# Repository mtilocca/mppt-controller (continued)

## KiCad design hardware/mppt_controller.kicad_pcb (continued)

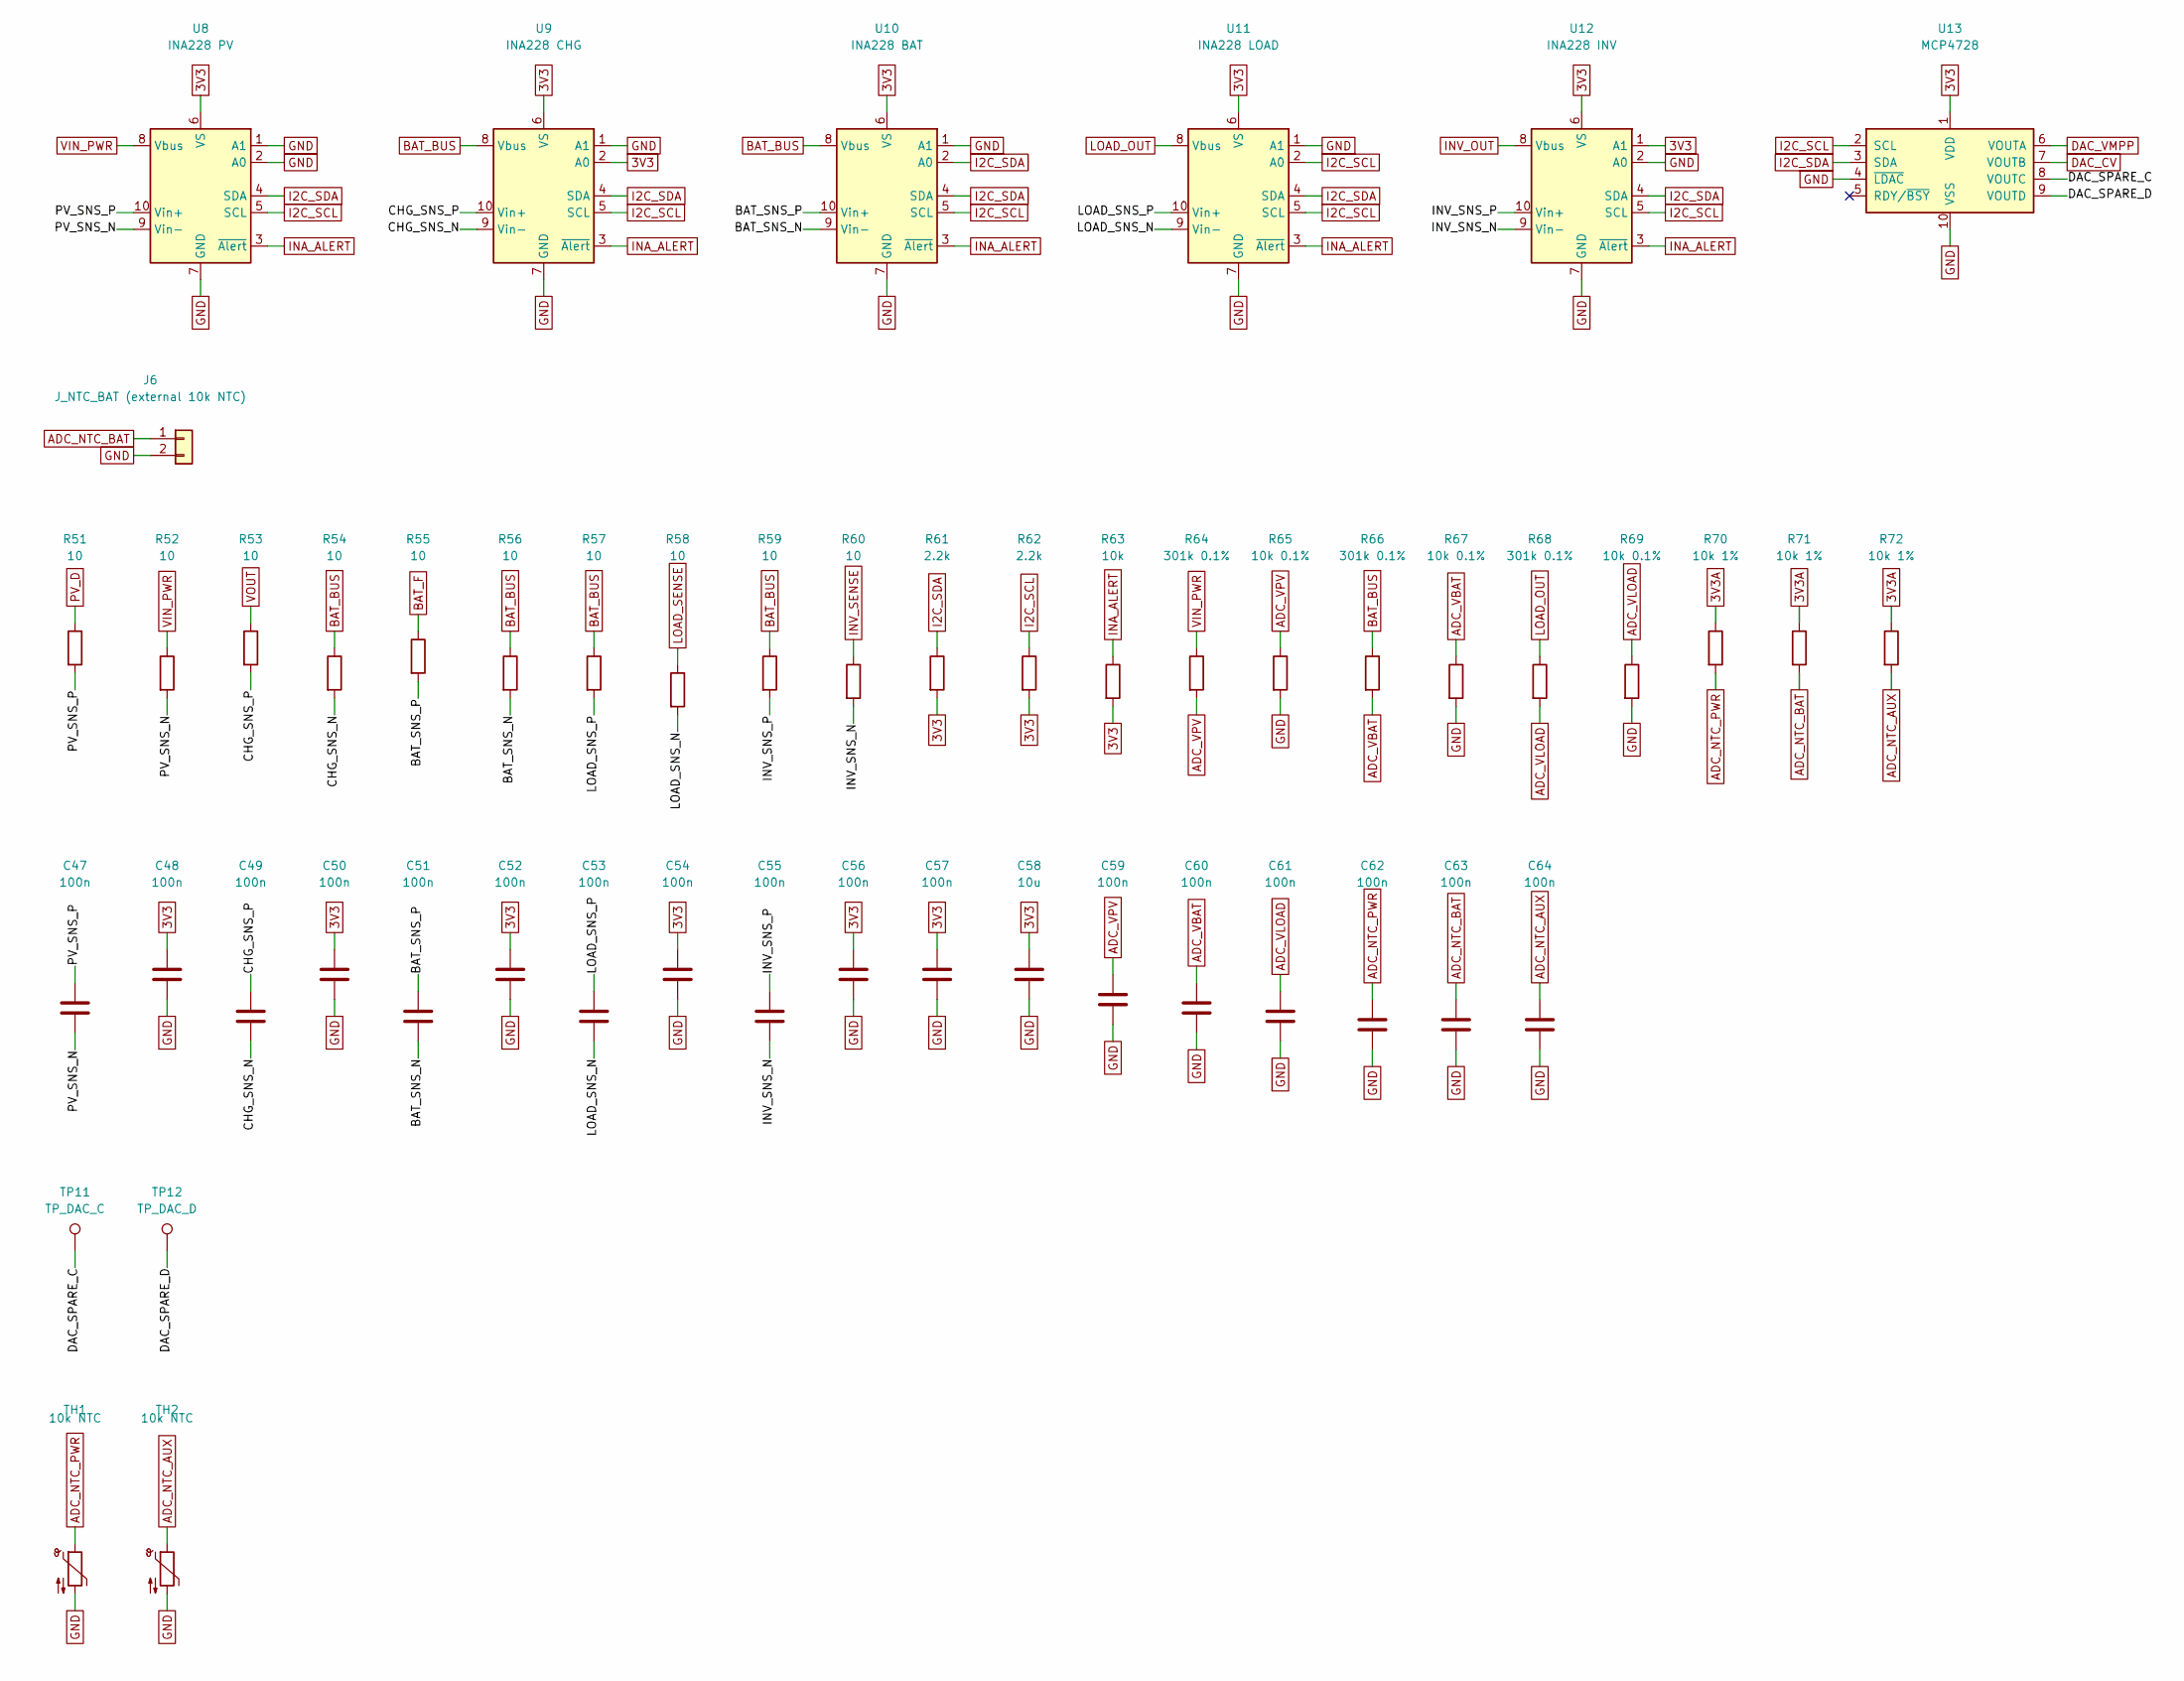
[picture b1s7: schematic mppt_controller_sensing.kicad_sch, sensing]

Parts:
C47, C48, C49, C50, C51, C52, C53, C54, C55, C56, C57, C59, C60, C61, C62, C63, C64: 100n; C_0603_1608Metric
C58: 10u; C_0805_2012Metric
J6: J_NTC_BAT (external 10k NTC); PinHeader_1x02_P2.54mm_Vertical
R51, R52, R53, R54, R55, R56, R57, R58, R59, R60: 10; R_0603_1608Metric
R61, R62: 2.2k; R_0603_1608Metric
R63: 10k; R_0603_1608Metric
R64, R66, R68: 301k 0.1%; R_0603_1608Metric
R65, R67, R69: 10k 0.1%; R_0603_1608Metric
R70, R71, R72: 10k 1%; R_0603_1608Metric
TH1, TH2: 10k NTC; R_0603_1608Metric
TP11: TP_DAC_C; TestPoint_Pad_D1.5mm
TP12: TP_DAC_D; TestPoint_Pad_D1.5mm
U8: INA228 PV; MSOP-10_3x3mm_P0.5mm
U9: INA228 CHG; MSOP-10_3x3mm_P0.5mm
U10: INA228 BAT; MSOP-10_3x3mm_P0.5mm
U11: INA228 LOAD; MSOP-10_3x3mm_P0.5mm
U12: INA228 INV; MSOP-10_3x3mm_P0.5mm
U13: MCP4728; MSOP-10_3x3mm_P0.5mm

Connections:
3V3: C48.1, C50.1, C52.1, C54.1, C56.1, C57.1, C58.1, R61.2, R62.2, R63.2, U8.6 (VS), U9.2 (A0), U9.6 (VS), U10.6 (VS), U11.6 (VS), U12.1 (A1), U12.6 (VS), U13.1 (VDD); also elsewhere on the board
3V3A: R70.1, R71.1, R72.1; also elsewhere on the board
/sensing/BAT_SNS_N: C51.2, R56.2, U10.9 (Vin-)
/sensing/BAT_SNS_P: C51.1, R55.2, U10.10 (Vin+)
/sensing/CHG_SNS_N: C49.2, R54.2, U9.9 (Vin-)
/sensing/CHG_SNS_P: C49.1, R53.2, U9.10 (Vin+)
/sensing/DAC_SPARE_C: TP11.1, U13.8 (VOUTC)
/sensing/DAC_SPARE_D: TP12.1, U13.9 (VOUTD)
/sensing/INV_SNS_N: C55.2, R60.2, U12.9 (Vin-)
/sensing/INV_SNS_P: C55.1, R59.2, U12.10 (Vin+)
/sensing/LOAD_SNS_N: C53.2, R58.2, U11.9 (Vin-)
/sensing/LOAD_SNS_P: C53.1, R57.2, U11.10 (Vin+)
/sensing/PV_SNS_N: C47.2, R52.2, U8.9 (Vin-)
/sensing/PV_SNS_P: C47.1, R51.2, U8.10 (Vin+)
ADC_NTC_AUX: C64.1, R72.2, TH2.1; also elsewhere on the board
ADC_NTC_BAT: C63.1, J6.1, R71.2; also elsewhere on the board
ADC_NTC_PWR: C62.1, R70.2, TH1.1; also elsewhere on the board
ADC_VBAT: C60.1, R66.2, R67.1; also elsewhere on the board
ADC_VLOAD: C61.1, R68.2, R69.1; also elsewhere on the board
ADC_VPV: C59.1, R64.2, R65.1; also elsewhere on the board
BAT_BUS: R54.1, R56.1, R57.1, R59.1, R66.1, U9.8 (Vbus), U10.8 (Vbus); also elsewhere on the board
BAT_F: R55.1; also elsewhere on the board
DAC_CV: U13.7 (VOUTB); also elsewhere on the board
DAC_VMPP: U13.6 (VOUTA); also elsewhere on the board
GND: C48.2, C50.2, C52.2, C54.2, C56.2, C57.2, C58.2, C59.2, C60.2, C61.2, C62.2, C63.2, C64.2, J6.2, R65.2, R67.2, R69.2, TH1.2, TH2.2, U8.1 (A1), U8.2 (A0), U8.7 (GND), U9.1 (A1), U9.7 (GND), U10.1 (A1), U10.7 (GND), U11.1 (A1), U11.7 (GND), U12.2 (A0), U12.7 (GND), U13.4 (~LDAC), U13.10 (VSS); also elsewhere on the board
I2C_SCL: R62.1, U8.5 (SCL), U9.5 (SCL), U10.5 (SCL), U11.2 (A0), U11.5 (SCL), U12.5 (SCL), U13.2 (SCL); also elsewhere on the board
I2C_SDA: R61.1, U8.4 (SDA), U9.4 (SDA), U10.2 (A0), U10.4 (SDA), U11.4 (SDA), U12.4 (SDA), U13.3 (SDA); also elsewhere on the board
INA_ALERT: R63.1, U8.3 (~Alert), U9.3 (~Alert), U10.3 (~Alert), U11.3 (~Alert), U12.3 (~Alert); also elsewhere on the board
INV_OUT: U12.8 (Vbus); also elsewhere on the board
INV_SENSE: R60.1; also elsewhere on the board
LOAD_OUT: R68.1, U11.8 (Vbus); also elsewhere on the board
LOAD_SENSE: R58.1; also elsewhere on the board
PV_D: R51.1; also elsewhere on the board
VIN_PWR: R52.1, R64.1, U8.8 (Vbus); also elsewhere on the board
VOUT: R53.1; also elsewhere on the board

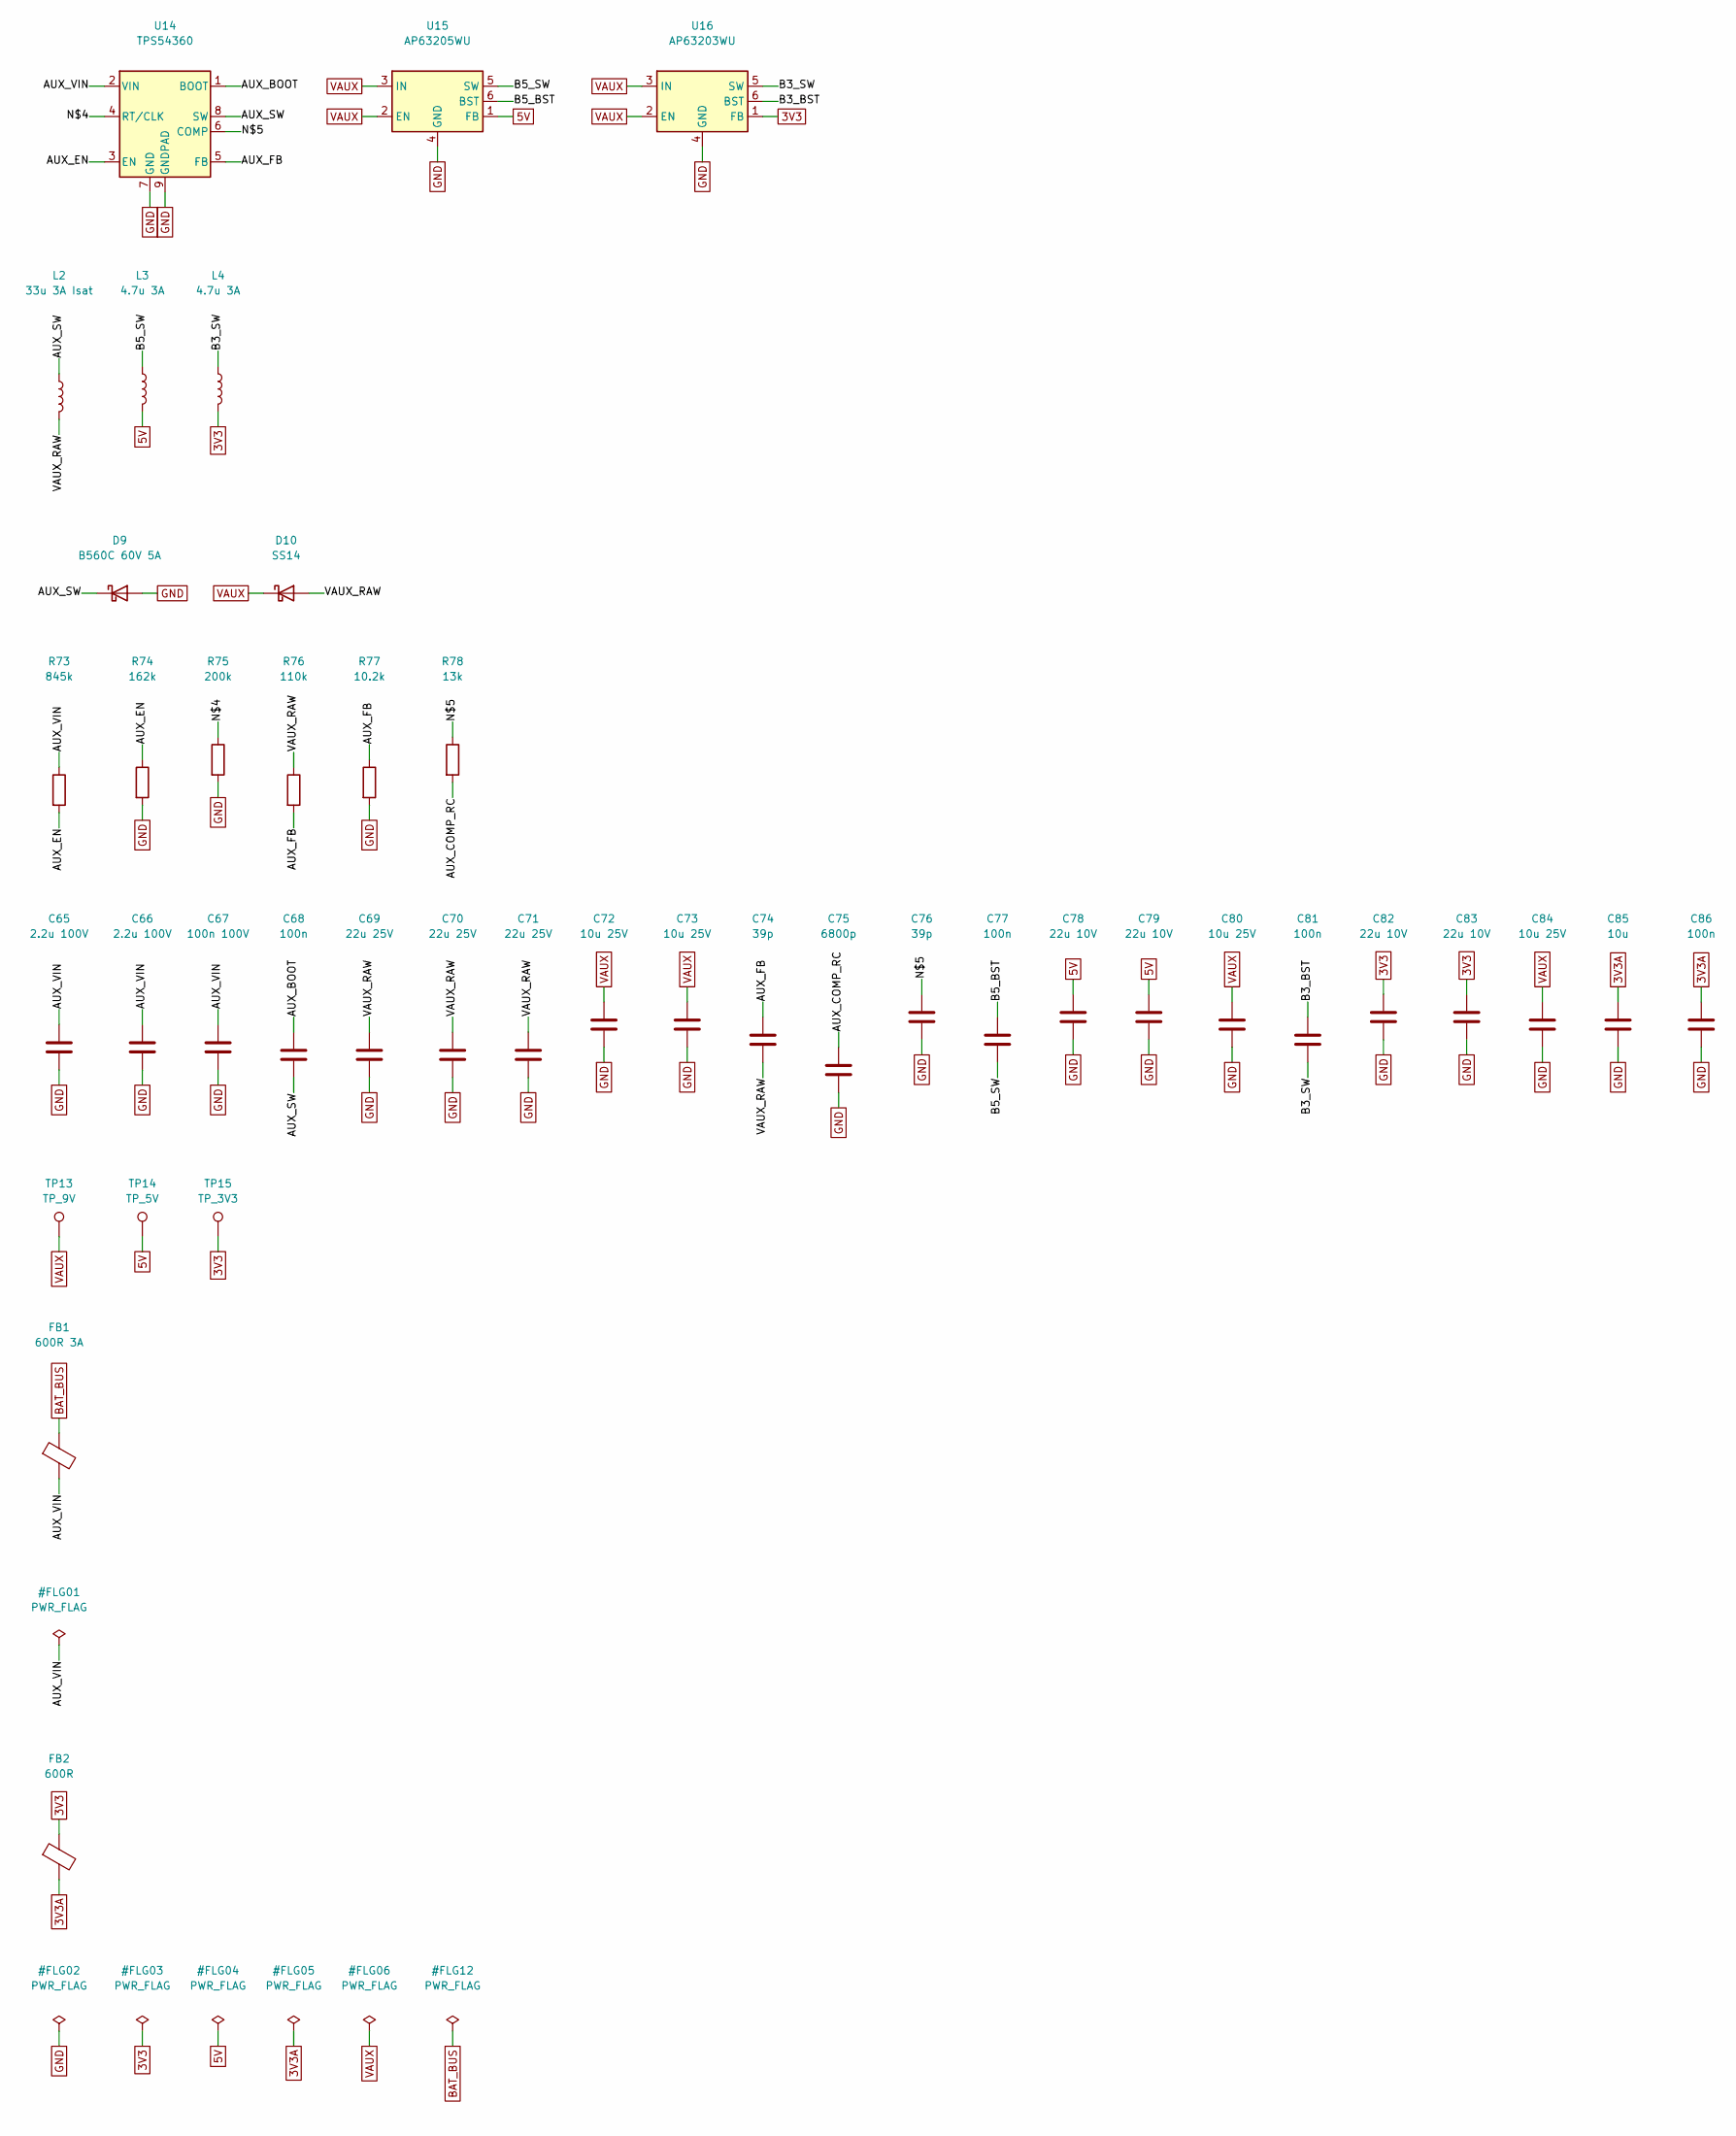
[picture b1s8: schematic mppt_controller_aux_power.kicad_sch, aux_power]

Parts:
C65, C66: 2.2u 100V; C_1210_3225Metric
C67: 100n 100V; C_0805_2012Metric
C68, C77, C81, C86: 100n; C_0603_1608Metric
C69, C70, C71: 22u 25V; C_1210_3225Metric
C72, C73, C80, C84: 10u 25V; C_1206_3216Metric
C74, C76: 39p; C_0603_1608Metric
C75: 6800p; C_0603_1608Metric
C78, C79, C82, C83: 22u 10V; C_1206_3216Metric
C85: 10u; C_0805_2012Metric
D9: B560C 60V 5A; D_SMC
D10: SS14; D_SMA
FB1: 600R 3A; L_1206_3216Metric
FB2: 600R; L_0603_1608Metric
L2: 33u 3A Isat; L_Bourns_SRP1245A
L3, L4: 4.7u 3A; L_Bourns_SRP5030T
R73: 845k; R_0603_1608Metric
R74: 162k; R_0603_1608Metric
R75: 200k; R_0603_1608Metric
R76: 110k; R_0603_1608Metric
R77: 10.2k; R_0603_1608Metric
R78: 13k; R_0603_1608Metric
TP13: TP_9V; TestPoint_Pad_D1.5mm
TP14: TP_5V; TestPoint_Pad_D1.5mm
TP15: TP_3V3; TestPoint_Pad_D1.5mm
U14: TPS54360; HSOP-8-1EP_3.9x4.9mm_P1.27mm_EP2.41x3.1mm
U15: AP63205WU; TSOT-23-6
U16: AP63203WU; TSOT-23-6

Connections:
3V3: C82.1, C83.1, FB2.1, L4.2, TP15.1, U16.1 (FB); also elsewhere on the board
3V3A: C85.1, C86.1, FB2.2; also elsewhere on the board
5V: C78.1, C79.1, L3.2, TP14.1, U15.1 (FB); also elsewhere on the board
/aux_power/AUX_BOOT: C68.1, U14.1 (BOOT)
/aux_power/AUX_COMP_RC: C75.1, R78.2
/aux_power/AUX_EN: R73.2, R74.1, U14.3 (EN)
/aux_power/AUX_FB: C74.1, R76.2, R77.1, U14.5 (FB)
/aux_power/AUX_SW: C68.2, D9.1 (K), L2.1, U14.8 (SW)
/aux_power/AUX_VIN: C65.1, C66.1, C67.1, FB1.2, R73.1, U14.2 (VIN)
/aux_power/B3_BST: C81.1, U16.6 (BST)
/aux_power/B3_SW: C81.2, L4.1, U16.5 (SW)
/aux_power/B5_BST: C77.1, U15.6 (BST)
/aux_power/B5_SW: C77.2, L3.1, U15.5 (SW)
/aux_power/N$4: R75.1, U14.4 (RT/CLK)
/aux_power/N$5: C76.1, R78.1, U14.6 (COMP)
/aux_power/VAUX_RAW: C69.1, C70.1, C71.1, C74.2, D10.2 (A), L2.2, R76.1
BAT_BUS: FB1.1; also elsewhere on the board
GND: C65.2, C66.2, C67.2, C69.2, C70.2, C71.2, C72.2, C73.2, C75.2, C76.2, C78.2, C79.2, C80.2, C82.2, C83.2, C84.2, C85.2, C86.2, D9.2 (A), R74.2, R75.2, R77.2, U14.7 (GND), U14.9 (GNDPAD), U15.4 (GND), U16.4 (GND); also elsewhere on the board
VAUX: C72.1, C73.1, C80.1, C84.1, D10.1 (K), TP13.1, U15.2 (EN), U15.3 (IN), U16.2 (EN), U16.3 (IN); also elsewhere on the board

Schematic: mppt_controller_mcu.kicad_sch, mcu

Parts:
C87, C88: 2.2u; C_0603_1608Metric
C89, C90, C91, C92, C93, C94, C95, C96, C97, C98, C99, C103, C104: 100n; C_0603_1608Metric
C100, C101: 4.7u; C_0805_2012Metric
C102: 1u; C_0603_1608Metric
C105, C106: 12p; C_0603_1608Metric
C107, C108: 8p; C_0603_1608Metric
J7: J_SWD (Cortex 1.27 mm); PinHeader_2x05_P1.27mm_Vertical
R79: 10k; R_0603_1608Metric
R80: 1k; R_0603_1608Metric
SW1: RESET; SW_SPST_PTS645Sx43SMTR92
SW2: BOOT0; SW_SPST_PTS645Sx43SMTR92
U17: STM32H743ZIT6; LQFP-144_20x20mm_P0.5mm
Y1: 25MHz 8pF; Crystal_SMD_3225-4Pin_3.2x2.5mm
Y2: 32.768kHz 6pF; Crystal_SMD_3215-2Pin_3.2x1.5mm

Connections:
3V3: C89.1, C90.1, C91.1, C92.1, C93.1, C94.1, C95.1, C96.1, C97.1, C98.1, C99.1, C100.1, C101.1, J7.1, R80.2, U17.6 (VBAT), U17.17 (VDD), U17.30 (VDD), U17.39 (VDD), U17.52 (VDD), U17.62 (VDD), U17.72 (VDD), U17.84 (VDD), U17.95 (VDD33_USB), U17.108 (VDD), U17.121 (VDD), U17.131 (VDD), U17.143 (PDR_ON), U17.144 (VDD); also elsewhere on the board
3V3A: C102.1, C103.1, U17.32 (VREF+), U17.33 (VDDA); also elsewhere on the board
/mcu/BOOT0: R79.1, SW2.1, U17.138 (BOOT0)
/mcu/LSE_IN: C107.1, U17.8 (PC14), Y2.1
/mcu/LSE_OUT: C108.1, U17.9 (PC15), Y2.2
/mcu/N$6: R80.1, SW2.2
/mcu/NRST: C104.1, J7.10, SW1.1, U17.25 (NRST)
/mcu/OSC_IN: C105.1, U17.23 (PH0), Y1.1
/mcu/OSC_OUT: C106.1, U17.24 (PH1), Y1.3
/mcu/SWCLK: J7.4, U17.109 (PA14)
/mcu/SWDIO: J7.2, U17.105 (PA13)
/mcu/VCAP: C87.1, C88.1, U17.71 (VCAP), U17.106 (VCAP)
ADC_NTC_AUX: U17.19 (PF7); also elsewhere on the board
ADC_NTC_BAT: U17.13 (PF3); also elsewhere on the board
ADC_NTC_PWR: U17.50 (PF12); also elsewhere on the board
ADC_VBAT: U17.14 (PF4); also elsewhere on the board
ADC_VLOAD: U17.15 (PF5); also elsewhere on the board
ADC_VPV: U17.49 (PF11); also elsewhere on the board
CAN_RX: U17.114 (PD0); also elsewhere on the board
CAN_TX: U17.115 (PD1); also elsewhere on the board
CON_RX: U17.78 (PD9); also elsewhere on the board
CON_TX: U17.77 (PD8); also elsewhere on the board
ETH_CRS_DV: U17.43 (PA7); also elsewhere on the board
ETH_MDC: U17.27 (PC1); also elsewhere on the board
ETH_MDIO: U17.36 (PA2); also elsewhere on the board
ETH_NRST: U17.99 (PC9); also elsewhere on the board
ETH_REF_CLK: U17.35 (PA1); also elsewhere on the board
ETH_RXD0: U17.44 (PC4); also elsewhere on the board
ETH_RXD1: U17.45 (PC5); also elsewhere on the board
ETH_TXD0: U17.128 (PG13); also elsewhere on the board
ETH_TXD1: U17.127 (PG12); also elsewhere on the board
ETH_TX_EN: U17.126 (PG11); also elsewhere on the board
FAN_PWM: U17.100 (PA8); also elsewhere on the board
GND: C87.2, C88.2, C89.2, C90.2, C91.2, C92.2, C93.2, C94.2, C95.2, C96.2, C97.2, C98.2, C99.2, C100.2, C101.2, C102.2, C103.2, C104.2, C105.2, C106.2, C107.2, C108.2, J7.3, J7.5, J7.9, R79.2, SW1.2, U17.16 (VSS), U17.31 (VSSA), U17.38 (VSS), U17.51 (VSS), U17.61 (VSS), U17.83 (VSS), U17.94 (VSS), U17.107 (VSS), U17.120 (VSS), U17.130 (VSS), Y1.2 (G), Y1.4 (G); also elsewhere on the board
I2C_SCL: U17.136 (PB6); also elsewhere on the board
I2C_SDA: U17.137 (PB7); also elsewhere on the board
INA_ALERT: U17.111 (PC10); also elsewhere on the board
INV_FAULT: U17.112 (PC11); also elsewhere on the board
INV_NEN: U17.118 (PD4); also elsewhere on the board
INV_PGD: U17.116 (PD2); also elsewhere on the board
INV_REMOTE: U17.113 (PC12); also elsewhere on the board
LCD_B3: U17.79 (PD10); also elsewhere on the board
LCD_B4: U17.65 (PE12); also elsewhere on the board
LCD_B5: U17.37 (PA3); also elsewhere on the board
LCD_B6: U17.139 (PB8); also elsewhere on the board
LCD_B7: U17.140 (PB9); also elsewhere on the board
LCD_BL_PWM: U17.86 (PD15); also elsewhere on the board
LCD_CLK: U17.67 (PE14); also elsewhere on the board
LCD_DE: U17.66 (PE13); also elsewhere on the board
LCD_G2: U17.42 (PA6); also elsewhere on the board
LCD_G3: U17.64 (PE11); also elsewhere on the board
LCD_G4: U17.69 (PB10); also elsewhere on the board
LCD_G5: U17.70 (PB11); also elsewhere on the board
LCD_G6: U17.97 (PC7); also elsewhere on the board
LCD_G7: U17.117 (PD3); also elsewhere on the board
LCD_HSYNC: U17.96 (PC6); also elsewhere on the board
LCD_R3: U17.46 (PB0); also elsewhere on the board
LCD_R4: U17.41 (PA5); also elsewhere on the board
LCD_R5: U17.26 (PC0); also elsewhere on the board
LCD_R6: U17.47 (PB1); also elsewhere on the board
LCD_R7: U17.68 (PE15); also elsewhere on the board
LCD_RST: U17.98 (PC8); also elsewhere on the board
LCD_VSYNC: U17.40 (PA4); also elsewhere on the board
LED1: U17.141 (PE0); also elsewhere on the board
LED2: U17.85 (PD14); also elsewhere on the board
LED3: U17.82 (PD13); also elsewhere on the board
LED4: U17.81 (PD12); also elsewhere on the board
LOAD_NEN: U17.122 (PD6); also elsewhere on the board
LOAD_PGD: U17.119 (PD5); also elsewhere on the board
MPPT_NEN: U17.80 (PD11); also elsewhere on the board
MPPT_NFLT: U17.123 (PD7); also elsewhere on the board
QSPI_CLK: U17.22 (PF10); also elsewhere on the board
QSPI_IO0: U17.20 (PF8); also elsewhere on the board
QSPI_IO1: U17.21 (PF9); also elsewhere on the board
QSPI_IO2: U17.1 (PE2); also elsewhere on the board
QSPI_IO3: U17.18 (PF6); also elsewhere on the board
QSPI_NCS: U17.91 (PG6); also elsewhere on the board
RS485_DE: U17.93 (PG8); also elsewhere on the board
RS485_NRE: U17.34 (PA0); also elsewhere on the board
RS485_RX: U17.124 (PG9); also elsewhere on the board
RS485_TX: U17.129 (PG14); also elsewhere on the board
SPI_CS: U17.48 (PB2); also elsewhere on the board
SPI_DC: U17.102 (PA10); also elsewhere on the board
SPI_MISO: U17.75 (PB14); also elsewhere on the board
SPI_MOSI: U17.76 (PB15); also elsewhere on the board
SPI_RST: U17.101 (PA9); also elsewhere on the board
SPI_SCK: U17.74 (PB13); also elsewhere on the board
TOUCH_CS: U17.135 (PB5); also elsewhere on the board
TOUCH_INT: U17.73 (PB12); also elsewhere on the board
USB_DN: U17.103 (PA11); also elsewhere on the board
USB_DP: U17.104 (PA12); also elsewhere on the board
USB_VBUS: U17.142 (PE1); also elsewhere on the board

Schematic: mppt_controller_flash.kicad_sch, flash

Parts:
C109: 100n; C_0603_1608Metric
R81: 10k; R_0603_1608Metric
U18: W25Q128JVSIQ; SOIC-8_5.3x5.3mm_P1.27mm

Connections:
3V3: C109.1, R81.2, U18.8 (VCC); also elsewhere on the board
GND: C109.2, U18.4 (GND); also elsewhere on the board
QSPI_CLK: U18.6 (CLK); also elsewhere on the board
QSPI_IO0: U18.5 (DI/IO_{0}); also elsewhere on the board
QSPI_IO1: U18.2 (DO/IO_{1}); also elsewhere on the board
QSPI_IO2: U18.3 (~WP/IO_{2}); also elsewhere on the board
QSPI_IO3: U18.7 (~HOLD/~RESET/IO_{3}); also elsewhere on the board
QSPI_NCS: R81.1, U18.1 (~CS); also elsewhere on the board

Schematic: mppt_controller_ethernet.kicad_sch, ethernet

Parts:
C110: 1u; C_0603_1608Metric
C111: 470p; C_0603_1608Metric
C112, C113, C114, C117, C118: 100n; C_0603_1608Metric
C115, C116: 22p; C_0603_1608Metric
C119: 10u; C_0805_2012Metric
C120: 4.7n 2kV; C_1206_3216Metric
FB3: 600R; L_0603_1608Metric
J8: J_ETH HR911105A; RJ45_Hanrun_HR911105A_Horizontal
R82: 12.1k 1%; R_0603_1608Metric
R83, R86, R87: 10k; R_0603_1608Metric
R84: 33; R_0603_1608Metric
R85: 1.5k; R_0603_1608Metric
R88: 1M; R_0603_1608Metric
U19: LAN8720A; QFN-24-1EP_4x4mm_P0.5mm_EP2.6x2.6mm
Y3: 25MHz 20pF; Crystal_SMD_3225-4Pin_3.2x2.5mm

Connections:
3V3: C112.1, C113.1, C114.1, FB3.1, R85.2, R86.2, U19.1 (VDD2A), U19.9 (VDDIO), U19.19 (VDD1A); also elsewhere on the board
/ethernet/ETH_CT: C117.1, C118.1, C119.1, FB3.2, J8.4 (TCT), J8.5 (RCT)
/ethernet/ETH_SHIELD: C120.1, J8.SH, R88.1
/ethernet/N$7: R82.1, U19.24 (RBIAS)
/ethernet/N$8: R83.1, U19.2 (LED2/~INTSEL)
/ethernet/N$9: R84.1, U19.14 (~INT/REFCLKO)
/ethernet/N$10: J8.1 (TD+), U19.21 (TXP)
/ethernet/N$11: J8.2 (TD-), U19.20 (TXN)
/ethernet/N$12: J8.3 (RD+), U19.23 (RXP)
/ethernet/N$13: J8.6 (RD-), U19.22 (RXN)
/ethernet/PHY_RXER: R87.1, U19.10 (RXER/PHYAD0)
/ethernet/PHY_VDDCR: C110.1, C111.1, U19.6 (VDDCR)
/ethernet/PHY_XTAL1: C115.1, U19.5 (XTAL1/CLKIN), Y3.1
/ethernet/PHY_XTAL2: C116.1, U19.4 (XTAL2), Y3.3
ETH_CRS_DV: U19.11 (CRS_DV/MODE2); also elsewhere on the board
ETH_MDC: U19.13 (MDC); also elsewhere on the board
ETH_MDIO: R85.1, U19.12 (MDIO); also elsewhere on the board
ETH_NRST: R86.1, U19.15 (~RST); also elsewhere on the board
ETH_REF_CLK: R84.2; also elsewhere on the board
ETH_RXD0: U19.8 (RXD0/MODE0); also elsewhere on the board
ETH_RXD1: U19.7 (RXD1/MODE1); also elsewhere on the board
ETH_TXD0: U19.17 (TXD0); also elsewhere on the board
ETH_TXD1: U19.18 (TXD1); also elsewhere on the board
ETH_TX_EN: U19.16 (TXEN); also elsewhere on the board
GND: C110.2, C111.2, C112.2, C113.2, C114.2, C115.2, C116.2, C117.2, C118.2, C119.2, C120.2, R82.2, R83.2, R87.2, R88.2, U19.25 (VSS), Y3.2 (G), Y3.4 (G); also elsewhere on the board

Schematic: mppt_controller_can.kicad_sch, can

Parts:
C121, C123, C124: 100n; C_0603_1608Metric
C122, C125: 10u; C_0805_2012Metric
D11: SM712; SOT-23
J9: J_CAN (H, L, GND); TerminalBlock_Phoenix_PT-1,5-3-3.5-H_1x03_P3.50mm_Horizontal
JP2: JP_CAN_TERM; SolderJumper-2_P1.3mm_Open_Pad1.0x1.5mm
R89: 120; R_0603_1608Metric
U20: CA-IS3062VW; SOIC-16W_7.5x10.3mm_P1.27mm

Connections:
3V3: C123.1, U20.7 (VCCL); also elsewhere on the board
5V: C121.1, C122.1, U20.1 (VCC); also elsewhere on the board
/can/CANH: D11.1 (A1), J9.1, R89.1, U20.13 (CANH)
/can/CANL: D11.2 (A2), J9.2, JP2.2 (B), U20.12 (CANL)
/can/CAN_GND: C124.2, C125.2, D11.3 (common), J9.3, U20.9 (GND2), U20.10 (GND2), U20.15 (GND2)
/can/CAN_TERM_MID: JP2.1 (A), R89.2
/can/CAN_VISO: C124.1, C125.1, U20.11 (VISO), U20.16 (VISO)
CAN_RX: U20.5 (RXD); also elsewhere on the board
CAN_TX: U20.3 (TXD); also elsewhere on the board
GND: C121.2, C122.2, C123.2, U20.2 (GND1), U20.8 (GND1); also elsewhere on the board

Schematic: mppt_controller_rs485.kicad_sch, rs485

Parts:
C126, C128: 100n; C_0603_1608Metric
C127, C129: 10u; C_0805_2012Metric
D12: SM712; SOT-23
J10: J_485 (A, B, GND); TerminalBlock_Phoenix_PT-1,5-3-3.5-H_1x03_P3.50mm_Horizontal
JP3: JP_485_TERM; SolderJumper-2_P1.3mm_Open_Pad1.0x1.5mm
R90: 120; R_0603_1608Metric
U21: CA-IS3092W; SOIC-16W_7.5x10.3mm_P1.27mm

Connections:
3V3: C126.1, C127.1, U21.1 (VCC); also elsewhere on the board
/rs485/ISO_3V3: C128.1, C129.1, U21.16 (VISO)
/rs485/ISO_GND: C128.2, C129.2, D12.3 (common), J10.3, U21.9 (GNDB), U21.15 (GNDB)
/rs485/RS485_A: D12.1 (A1), J10.1, R90.1, U21.12 (A)
/rs485/RS485_B: D12.2 (A2), J10.2, JP3.2 (B), U21.13 (B)
/rs485/RS485_TERM_MID: JP3.1 (A), R90.2
GND: C126.2, C127.2, U21.2 (GNDA), U21.8 (GNDA); also elsewhere on the board
RS485_DE: U21.5 (DE); also elsewhere on the board
RS485_NRE: U21.4 (~RE); also elsewhere on the board
RS485_RX: U21.3 (RO); also elsewhere on the board
RS485_TX: U21.6 (DI); also elsewhere on the board

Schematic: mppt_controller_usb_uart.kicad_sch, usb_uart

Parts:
C130: 4.7n; C_0603_1608Metric
C131: 10u; C_1206_3216Metric
D13: SS14; D_SMA
F3: PTC 0.5A 6V; Fuse_1206_3216Metric
J11: J_USB; USB_C_Receptacle_HRO_TYPE-C-31-M-12
J12: J_UART (GND, TX, RX, 3V3); PinHeader_1x04_P2.54mm_Vertical
R91, R92: 5.1k; R_0603_1608Metric
R93: 1M; R_0603_1608Metric
R94: 10k; R_0603_1608Metric
R95: 20k; R_0603_1608Metric
TP16: TP_USB_PWR; TestPoint_Pad_D1.5mm
U22: USBLC6-2SC6; SOT-23-6

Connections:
3V3: J12.4; also elsewhere on the board
/usb_uart/N$14: J11.A5 (CC1), R91.1
/usb_uart/N$15: J11.B5 (CC2), R92.1
/usb_uart/N$16: C130.1, J11.SH (SHIELD), R93.1
/usb_uart/USB_DN_CONN: J11.A7 (D-), J11.B7 (D-), U22.3 (I/O2)
/usb_uart/USB_DP_CONN: J11.A6 (D+), J11.B6 (D+), U22.1 (I/O1)
/usb_uart/VBUS: C131.1, F3.1, J11.A4 (VBUS), J11.A9 (VBUS), J11.B4 (VBUS), J11.B9 (VBUS), R94.1, U22.5 (VBUS)
/usb_uart/VBUS_PROT: D13.2 (A), F3.2, TP16.1
CON_RX: J12.3; also elsewhere on the board
CON_TX: J12.2; also elsewhere on the board
GND: C130.2, C131.2, J11.A1 (GND), J11.A12 (GND), J11.B1 (GND), J11.B12 (GND), J12.1, R91.2, R92.2, R93.2, R95.2, U22.2 (GND); also elsewhere on the board
USB_DN: U22.4 (I/O2); also elsewhere on the board
USB_DP: U22.6 (I/O1); also elsewhere on the board
USB_VBUS: R94.2, R95.1; also elsewhere on the board
VAUX: D13.1 (K); also elsewhere on the board

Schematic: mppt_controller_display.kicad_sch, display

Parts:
C132, C133, C134: 100n; C_0603_1608Metric
C135: 10u 25V; C_1206_3216Metric
C136: 10u 50V; C_1206_3216Metric
D14, D16: SS14; D_SMA
D15: BZT52C27 27V (OVP); D_SOD-123
J13: J_LCD 40-pin 0.5 mm FPC (4.3in RGB); Hirose_FH12-40S-0.5SH_1x40-1MP_P0.50mm_Horizontal
J14: J_SPI_LCD (GND, 3V3, SCK, MOSI, MISO, CS, DC, RST); PinHeader_1x08_P2.54mm_Vertical
J15: J_FAN (9 V, GND-switched); PinHeader_1x02_P2.54mm_Vertical
L5: 22u 1.5A; L_Bourns_SRP5030T
Q13: 2N7002; SOT-23
R96, R100, R101: 100k; R_0603_1608Metric
R97, R98: 10k; R_0603_1608Metric
R99: 30 1%; R_0603_1608Metric
U23: XPT2046; TSSOP-16_4.4x5mm_P0.65mm
U24: MT3608; SOT-23-6

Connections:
3V3: C132.1, C133.1, J13.4, J14.2, R97.2, R98.2, U23.1 (VCC), U23.7 (VBAT), U23.10 (IOVDD); also elsewhere on the board
5V: C135.1, L5.1, U24.5 (IN); also elsewhere on the board
/display/BL_SW: D14.2 (A), L5.2, U24.1 (SW)
/display/FAN_K: D16.2 (A), J15.2, Q13.3 (D)
/display/LCD_BL_A: C136.1, D14.1 (K), D15.1 (K), J13.2
/display/LCD_BL_K: J13.1, R99.1, U24.3 (FB)
/display/N$17: C134.1, U23.9 (VREF)
/display/TOUCH_XL: J13.39, U23.4 (XN)
/display/TOUCH_XR: J13.37, U23.2 (XP)
/display/TOUCH_YD: J13.38, U23.5 (YN)
/display/TOUCH_YU: J13.40, U23.3 (YP)
FAN_PWM: Q13.1 (G), R101.1; also elsewhere on the board
GND: C132.2, C133.2, C134.2, C135.2, C136.2, D15.2 (A), J13.3, J13.5, J13.6, J13.7, J13.13, J13.14, J13.21, J13.22, J13.23, J13.29, J13.36, J14.1, Q13.2 (S), R96.2, R99.2, R100.2, R101.2, U23.6 (GND), U23.8 (IN), U24.2 (GND); also elsewhere on the board
LCD_B3: J13.24; also elsewhere on the board
LCD_B4: J13.25; also elsewhere on the board
LCD_B5: J13.26; also elsewhere on the board
LCD_B6: J13.27; also elsewhere on the board
LCD_B7: J13.28; also elsewhere on the board
LCD_BL_PWM: R100.1, U24.4 (EN); also elsewhere on the board
LCD_CLK: J13.30; also elsewhere on the board
LCD_DE: J13.34; also elsewhere on the board
LCD_G2: J13.15; also elsewhere on the board
LCD_G3: J13.16; also elsewhere on the board
LCD_G4: J13.17; also elsewhere on the board
LCD_G5: J13.18; also elsewhere on the board
LCD_G6: J13.19; also elsewhere on the board
LCD_G7: J13.20; also elsewhere on the board
LCD_HSYNC: J13.32; also elsewhere on the board
LCD_R3: J13.8; also elsewhere on the board
LCD_R4: J13.9; also elsewhere on the board
LCD_R5: J13.10; also elsewhere on the board
LCD_R6: J13.11; also elsewhere on the board
LCD_R7: J13.12; also elsewhere on the board
LCD_RST: J13.31, R96.1; also elsewhere on the board
LCD_VSYNC: J13.33; also elsewhere on the board
SPI_CS: J14.6; also elsewhere on the board
SPI_DC: J14.7; also elsewhere on the board
SPI_MISO: J14.5, U23.12 (DOUT); also elsewhere on the board
SPI_MOSI: J14.4, U23.14 (DIN); also elsewhere on the board
SPI_RST: J14.8; also elsewhere on the board
SPI_SCK: J14.3, U23.16 (DCLK); also elsewhere on the board
TOUCH_CS: R97.1, U23.15 (~CS); also elsewhere on the board
TOUCH_INT: R98.1, U23.11 (~PENIRQ); also elsewhere on the board
VAUX: D16.1 (K), J15.1; also elsewhere on the board

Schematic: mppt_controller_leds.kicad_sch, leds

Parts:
D17: green; LED_0603_1608Metric
D18: yellow; LED_0603_1608Metric
D19: blue; LED_0603_1608Metric
D20: red; LED_0603_1608Metric
R102, R103, R104, R105: 1k; R_0603_1608Metric

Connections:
/leds/LED1_A: D17.2 (A), R102.2
/leds/LED2_A: D18.2 (A), R103.2
/leds/LED3_A: D19.2 (A), R104.2
/leds/LED4_A: D20.2 (A), R105.2
GND: D17.1 (K), D18.1 (K), D19.1 (K), D20.1 (K); also elsewhere on the board
LED1: R102.1; also elsewhere on the board
LED2: R103.1; also elsewhere on the board
LED3: R104.1; also elsewhere on the board
LED4: R105.1; also elsewhere on the board

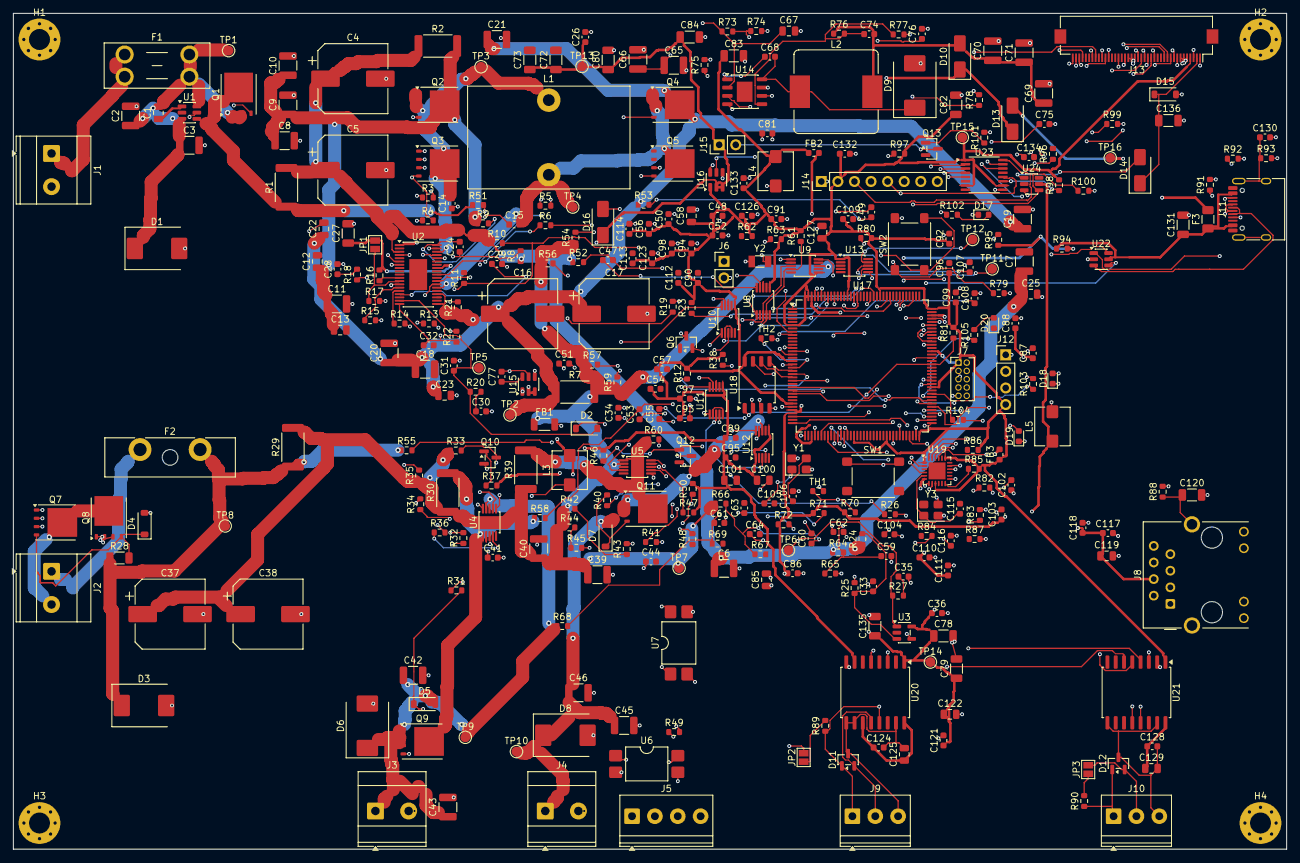
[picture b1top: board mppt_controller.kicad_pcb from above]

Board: 4 copper layers, 195.0 x 128.0 mm, 354 parts (0 on the bottom side), 230 nets.

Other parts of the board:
H1, H2, H3, H4: MountingHole_3.2mm_M3_Pad_Via
